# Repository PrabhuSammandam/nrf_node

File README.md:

# nrf_node
NRF node application.

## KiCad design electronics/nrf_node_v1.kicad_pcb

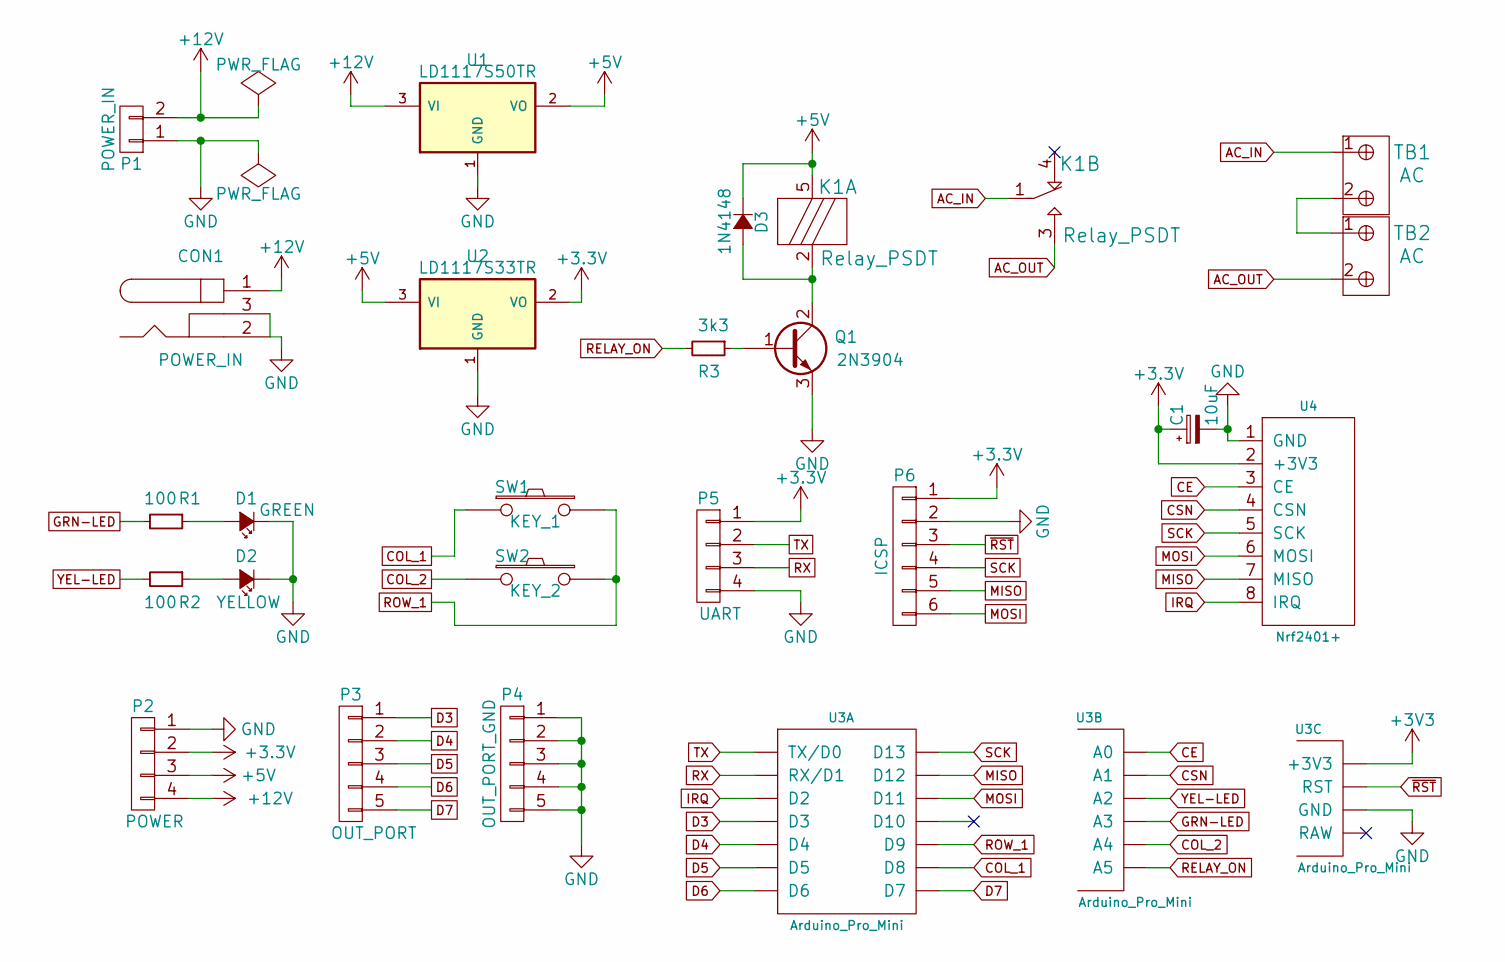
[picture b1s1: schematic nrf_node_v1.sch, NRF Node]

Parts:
C1: 10uF; C_0805_HandSoldering
CON1: POWER_IN; BARREL_JACK
D1: GREEN; LED-5MM
D2: YELLOW; LED-5MM
D3: 1N4148; SMA_Standard
K1: Relay_PSDT; Relay_SANYOU_SRD_Series_Form_C
P1: POWER_IN; Pin_Header_Straight_1x02
P2: POWER; Pin_Header_Straight_1x04
P3: OUT_PORT; Pin_Header_Straight_1x05
P4: OUT_PORT_GND; Pin_Header_Straight_1x05
P5: UART; Pin_Header_Straight_1x04
P6: ICSP; Pin_Header_Straight_1x06
Q1: 2N3904; SOT-23
R1, R2: 100; R_1206
R3: 3k3; R_1206
SW1: KEY_1; SW_TH_Tactile_Omron_B3F-10xx
SW2: KEY_2; SW_TH_Tactile_Omron_B3F-10xx
TB1, TB2: AC; TerminalBlock_Pheonix_MKDS1.5-2pol
U1: LD1117S50TR; SOT-223
U2: LD1117S33TR; SOT-223
U3: Arduino_Pro_Mini
U4: Nrf2401+

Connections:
+5V: D3.1 (K), K1.5 (1), P2.3, U1.2 (VO), U2.3 (VI)
+12V: CON1.1, P1.2, P2.4, U1.3 (VI)
AC_IN: K1.1 (C), TB1.1
AC_OUT: K1.3 (NO), TB2.2
CE: U3.A0, U4.3 (CE)
COL_1: SW1.1, U3.D8
COL_2: SW2.1, U3.A4
CSN: U3.A1, U4.4 (CSN)
D3: P3.1, U3.D3
D4: P3.2, U3.D4
D5: P3.3, U3.D5
D6: P3.4, U3.D6
D7: P3.5, U3.D7
GND: C1.2, CON1.2, CON1.3, D1.1 (K), D2.1 (K), P1.1, P2.1, P4.1, P4.2, P4.3, P4.4, P4.5, P5.4, P6.2, Q1.3 (E), U1.1 (GND), U2.1 (GND), U3.GND, U4.1 (GND)
GRN-LED: R1.2, U3.A3
IRQ: U3.D2, U4.8 (IRQ)
MISO: P6.5, U3.D12, U4.7 (MISO)
MOSI: P6.6, U3.D11, U4.6 (MOSI)
unnamed: D1.2 (A), R1.1
unnamed: D2.2 (A), R2.1
unnamed: D3.2 (A), K1.2, Q1.2 (C)
unnamed: Q1.1 (B), R3.1
unnamed: TB1.2, TB2.1
RELAY_ON: R3.2, U3.A5
ROW_1: SW1.2, SW2.2, U3.D9
RX: P5.3, U3.RX (RX/D1)
SCK: P6.4, U3.D13, U4.5 (SCK)
TX: P5.2, U3.TX (TX/D0)
YEL-LED: R2.2, U3.A2
~RST~: P6.3, U3.RST

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
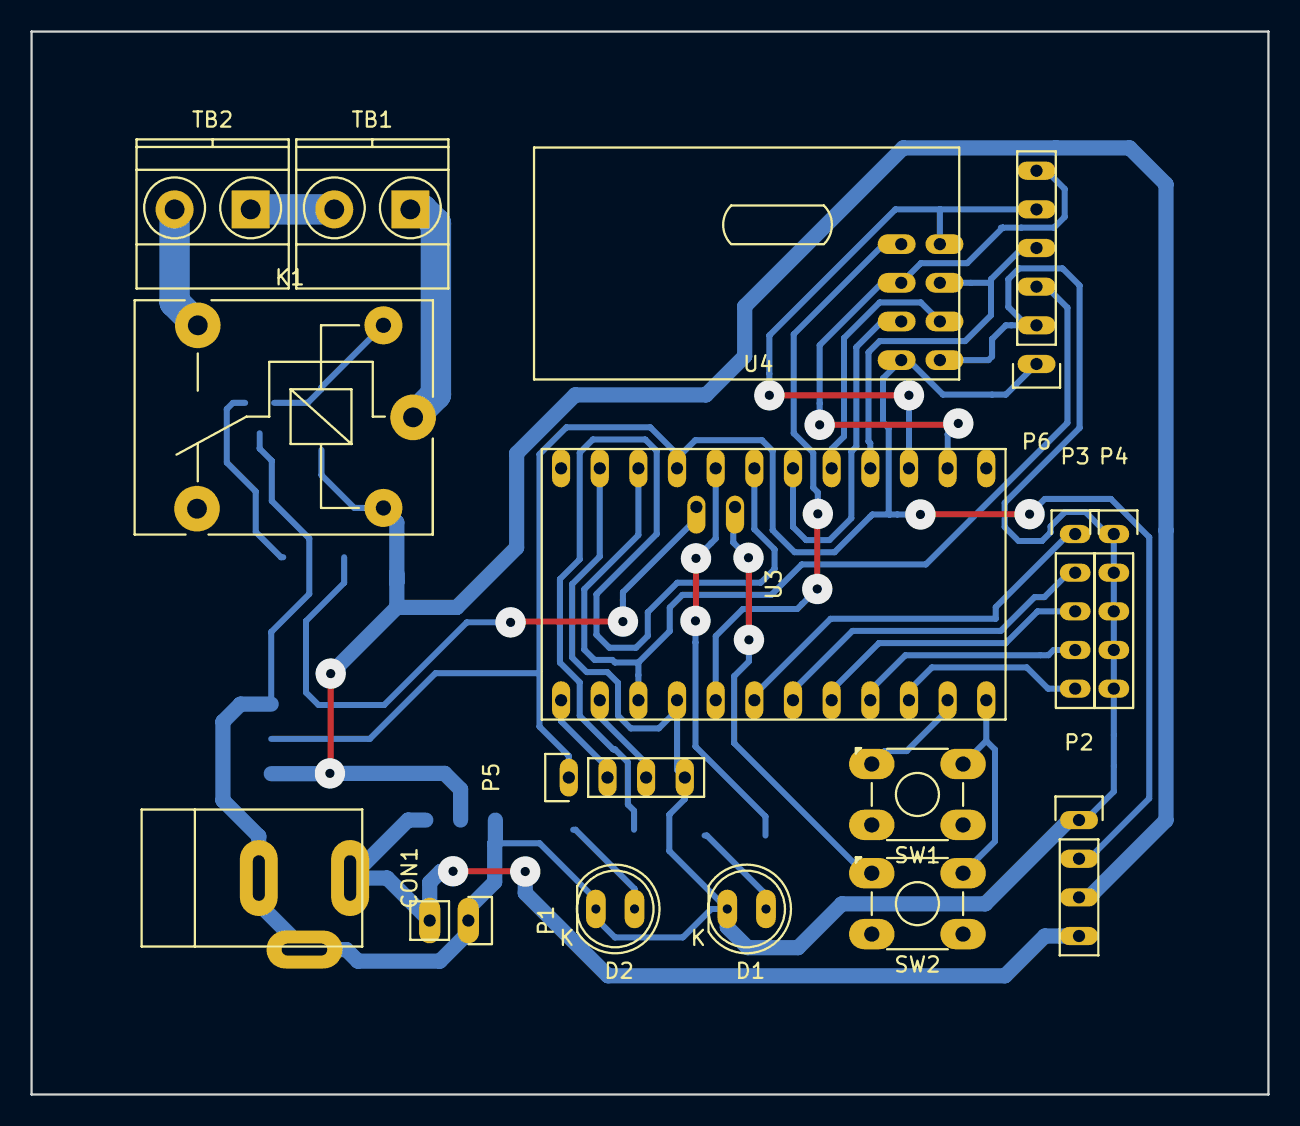
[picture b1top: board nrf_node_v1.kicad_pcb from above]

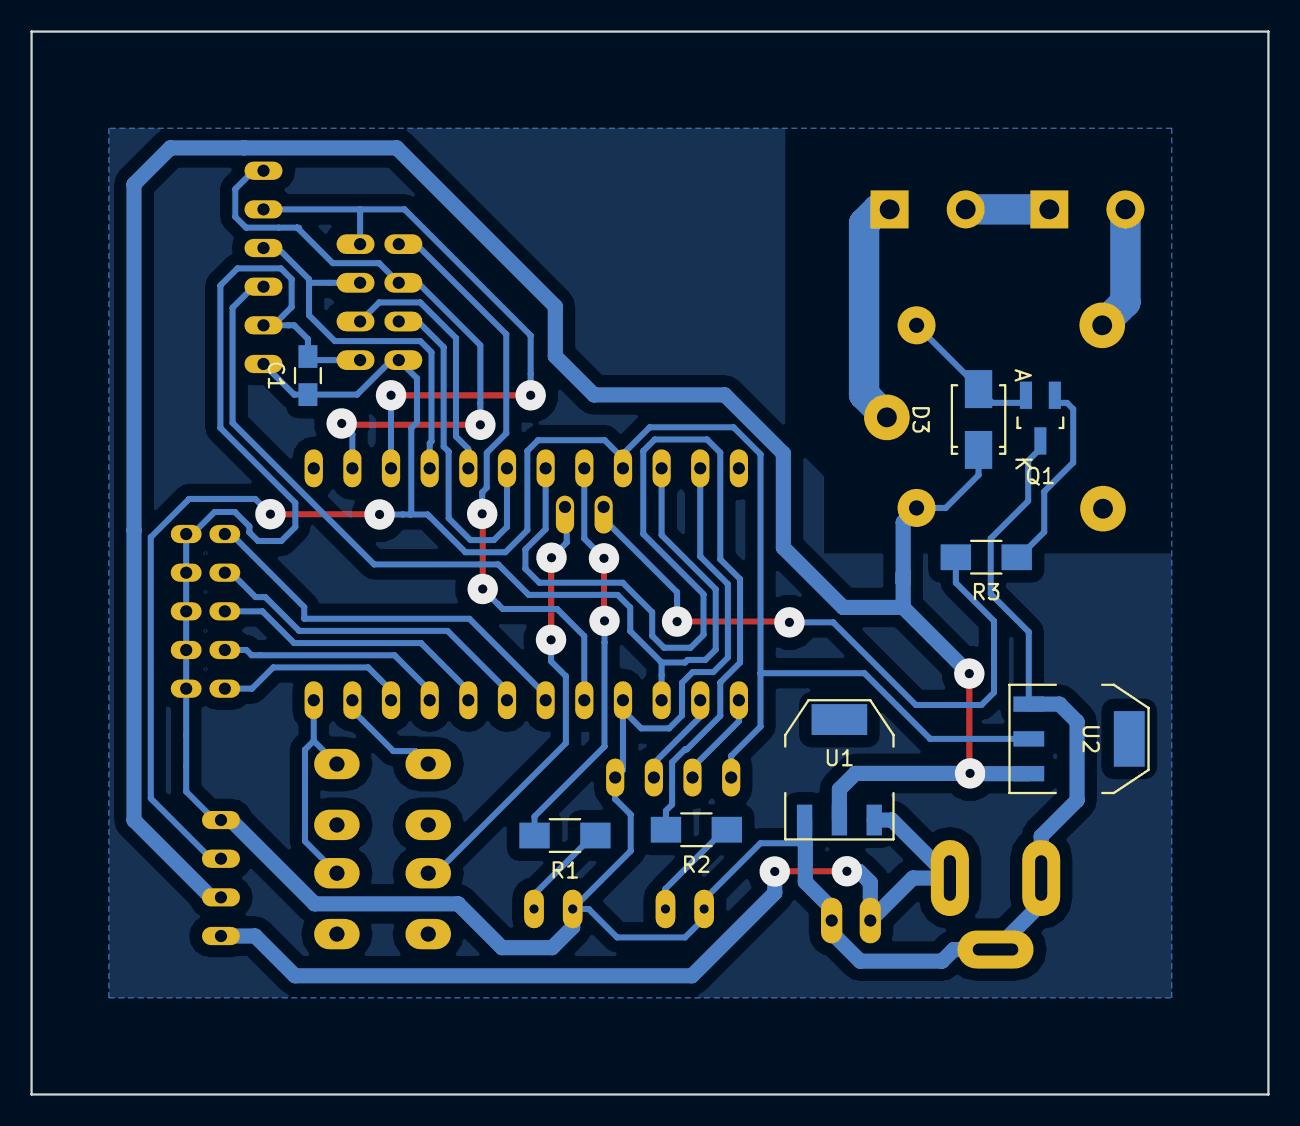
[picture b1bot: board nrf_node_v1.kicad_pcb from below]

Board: 2 copper layers, 81.3 x 69.8 mm, 24 parts (8 on the bottom side), 31 nets.

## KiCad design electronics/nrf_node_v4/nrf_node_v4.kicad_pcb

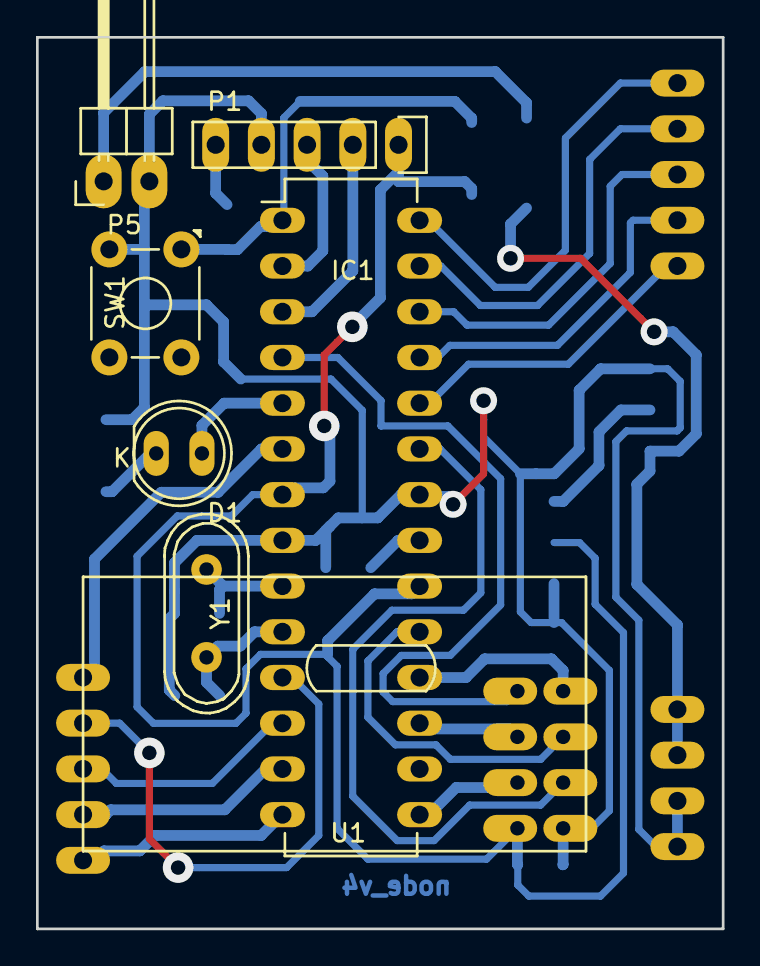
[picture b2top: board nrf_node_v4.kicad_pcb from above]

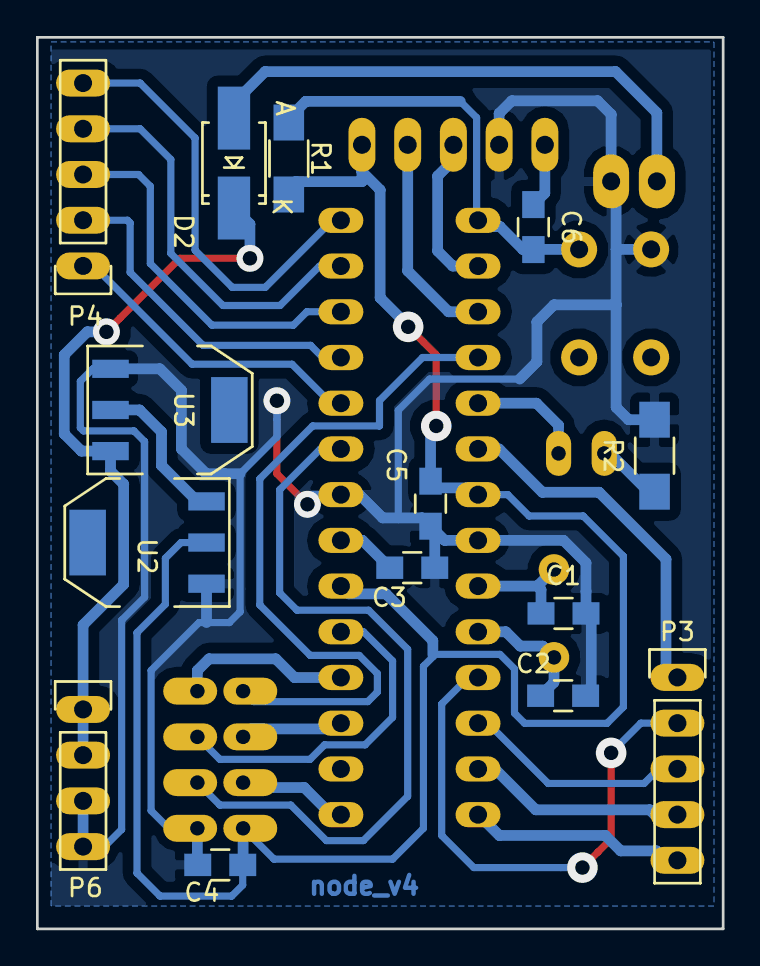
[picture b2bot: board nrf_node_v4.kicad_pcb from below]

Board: 2 copper layers, 38.1 x 49.5 mm, 21 parts (14 on the bottom side), 30 nets.

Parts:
C1, C2: 22pF; C_0805_HandSoldering
C3, C4, C5, C6: .1uF; C_0805_HandSoldering
D1: Led_Small; LED-5MM
D2: 1N4004; SMA_Handsoldering
IC1: ATMEGA328-P; DIP-28_W7.62mm_LongPads
P1: Serial; Pin_Header_Straight_1x05
P3, P4: CONN_01X05; Pin_Header_Straight_1x05
P5: PWR_IN; Pin_Header_Angled_1x02
P6: COMMON_1; Pin_Header_Straight_1x04
R1: 1k; R_1206_HandSoldering
R2: 100; R_1206_HandSoldering
SW1: RESET; SW_TH_Tactile_Omron_B3F-10xx
U1: Nrf2401+
U2: LD1117S33TR; SOT-223
U3: LD1117S50TR; SOT-223
Y1: 8MHZ; Crystal_HC49-U_Vertical

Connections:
+5V: U2.3, U3.2
+12V: D2.1, P6.1, P6.2, U3.3
/CE: IC1.23, U1.3
/CSN: IC1.15, U1.4
/IO-1: IC1.6, P3.1
/IO-2: IC1.11, P3.2
/IO-3: IC1.12, P3.3
/IO-4: IC1.13, P3.4
/IO-5: IC1.14, P3.5
/IO-6: IC1.24, P4.1
/IO-7: IC1.25, P4.2
/IO-8: IC1.26, P4.3
/IO-9: IC1.27, P4.4
/IO-10: IC1.28, P4.5
/IRQ: IC1.4, U1.8
/LED1: D1.2, IC1.5
/MISO: IC1.18, U1.7
/MOSI: IC1.17, U1.6
/OSC1: C1.1, IC1.9, Y1.1
/OSC2: C2.1, IC1.10, Y1.2
/RX: IC1.2, P1.3
/SCK: IC1.19, U1.5
/TX: IC1.3, P1.2
/Vin: D2.2, P5.1
/~RESET: C6.2, IC1.1, R1.2, SW1.1
GND: C1.2, C2.2, C3.2, C4.1, C5.2, IC1.8, IC1.22, P1.4, P5.2, P6.3, P6.4, R2.2, SW1.2, U1.1, U2.1, U3.1
unnamed: C3.1, IC1.21
unnamed: C6.1, P1.5
unnamed: D1.1, R2.1
VCC: C4.2, C5.1, IC1.7, IC1.20, P1.1, R1.1, U1.2, U2.2

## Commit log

2016-06-04 Added the files.
2016-06-04 reorganised
2016-06-04 Added Debug folder in ignore list
2016-06-04 Added the schematic and board file.
2016-06-20 Added version 3
2016-07-01 Added node version 4.
2016-07-12 Refactored code.
